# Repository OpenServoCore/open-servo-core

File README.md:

<p align="center">
  <picture>
    <source media="(prefers-color-scheme: dark)" srcset="docs/logo-dark.svg">
    
  </picture>
</p>

# OpenServoCore

> An open platform for turning cheap servos into smart actuators.

OpenServoCore (OSC) is open hardware and firmware that drops a CH32V006 control board into a $2-3 cloned hobby servo (SG90 and friends) and turns it into a Dynamixel-class smart actuator with position feedback, current sensing, bus addressing, and programmability. The bus speaks the **osc-native protocol**, a break-framed wire protocol designed to run whole on sub-$0.20 MCUs ([design writeup](https://aaronqian.com/log/2026-08-08-servo-protocol-stream-processing/)).

The thesis is the price point. At mass-production volume, an OSC swap board should add **no more than ~$1 to the BOM** of a cloned servo. That is cheap enough that upgrading every servo in a robot to smart becomes the default instead of a premium decision.

If you are here for a board, jump to [Boards](#boards). The firmware and its progress are in [Firmware](#firmware), and the design writeups are in [Reading](#reading).

## Status

**In active development. Nothing here is shippable yet.** What exists today:

- The **OSC Dev CH32** dev board is validated (Rev B) and you can order one.
- The firmware's protocol and bus transport are implemented and bench-proven on real silicon. Control loops are next.
- **[tinyboot](https://github.com/OpenServoCore/tinyboot)**, the OSC bootloader, has shipped v0.4.0 as its own repo.

The servo swap board (the one that goes inside a servo) is designed but not spun yet.

## Boards

**OSC Dev CH32** (`hardware/boards/osc-dev-v006/`) is the firmware development platform. It accepts any gutted hobby servo, takes power from USB-C, 1S-2S LiPo, or a WCH-LinkE, and fans out every rail and signal to edge test points. Rev B is validated. The [board README](hardware/boards/osc-dev-v006/README.md) has full schematics, pinouts, jumper behaviour, and bringup notes.

Want one? The full KiCad design files live in `hardware/boards/osc-dev-v006/`, ready to send to the board house of your choice.

There is also an experimental BLDC variant (`osc-dev-m007`) in the tree. It is unvalidated, so don't fab it.

## Firmware

The firmware is written in Rust and lives in `firmware/`. It is organized as chip-agnostic library crates (protocol, drivers, control table, discrete-event integration tests), a CH32 chip crate, and board binaries. The chip-agnostic layers compile and unit-test on a desktop with no hardware attached, and a discrete-event simulation runs the production crates ([the architecture writeup](https://aaronqian.com/log/2026-08-01-chip-agnostic-architecture-bare-metal-rust/) covers how).

What works today is the osc-native protocol and the servo bus transport. On the bench that means 0.5-3 Mbaud multi-servo status chains, ~30 µs ping turnaround at 1 Mbaud, and hardware CRC in both directions. The register-table conventions (flat control table, staged writes, alert semantics) will feel familiar if you have used Dynamixel. Control loops, persistence, and safety features are in progress, and build instructions will appear as the firmware matures.

Release and bench images are built with `scripts/build-image.sh <rev>` (add `--bench` for the bench-feature app, `--window` for the bench app with the window record). It exports the commit to one fixed directory (`$OSC_BUILD_ROOT`, default `~/.cache/osc-build`), builds every board image there and prints each image's sha1. The fixed path matters: cargo hashes the absolute path of each path dependency outside the workspace being built into crate metadata, rustc orders functions by the resulting symbol names, and so one commit built from two checkout paths links two layouts. On the V006 a layout shift moves timing by tens of cycles, so every image that is flashed, priced or compared comes from the script. [V006 performance](docs/v006-performance.md) covers the fetch model, the code-shape guards and how to measure a change.

The bootloader, [tinyboot](https://github.com/OpenServoCore/tinyboot), is a separate repo. It is part of the OSC firmware stack but versioned and released independently, and it supports more chips than the OSC boards on purpose (V003 / V00x / V103).

## Reading

The deep-dive writeups live on the blog:

- **[Stream processing on the wire](https://aaronqian.com/log/2026-08-08-servo-protocol-stream-processing/)**: the osc-native protocol design, and how the servo replies in tens of microseconds on a $0.16 chip.
- **[A chip-agnostic architecture for bare-metal embedded Rust](https://aaronqian.com/log/2026-08-01-chip-agnostic-architecture-bare-metal-rust/)**: the full firmware architecture, layer by layer, with code.
- **[Using the SPI peripheral as a DMA-fed CRC engine](https://aaronqian.com/log/2026-07-25-spi-as-dma-crc-engine/)**: hardware CRC on a chip with no CRC peripheral.
- **[HSI trim: calibrating a crystalless MCU over the bus](https://aaronqian.com/log/2026-07-18-hsi-trim-crystalless-mcu/)**: fleet clock calibration with nothing but the bus wire.
- **[Dynamixel 2.0 servo side: RX timing](https://aaronqian.com/log/2026-07-04-dynamixel-servo-side-rx-timing/)** and **[Fast Sync/Bulk Read](https://aaronqian.com/log/2026-07-11-dynamixel-servo-side-fast-sync-bulk-read/)**: the reference pair if you are building a Dynamixel-compatible device.

There is also one design doc in the repo worth reading. [Control theory](docs/control-theory.md) lays out the control design for the servo, with the cascaded loops, the estimators, and the sensing tiers. It is the plan, written ahead of the implementation, and it is not implemented yet.

## AI Use

I use AI heavily in this project. Claude (Fable 5, Opus 5, and earlier models) does a lot of the code generation and most of the document drafting, including parts of this README.

That does not make this vibe-coded. I review every line before it lands, and the result has to survive checks that don't care how the code was written. CI builds and tests every crate and cross-builds every board image. A discrete-event simulation runs the production crates and caught over a dozen real bugs before they reached silicon. The transport numbers above were measured on the bench. And this project was not built in one prompt. The history spans multiple years and many revisions of both the hardware and the firmware.

The documentation is more uneven than the code, and even this README could be easier to consume. That will improve, but working firmware comes first.

## Contributing

This is early. The most useful thing right now is **following along and asking questions** rather than opening PRs.

- **Discussions:** [github.com/OpenServoCore/open-servo-core/discussions](https://github.com/OpenServoCore/open-servo-core/discussions) is where design questions, ideas, and "is this on the roadmap?" go.
- **Build journey:** posts at [aaronqian.com](https://aaronqian.com) document the design decisions, dead ends, and what shipped each week.
- **Issues:** open ones are scoped to specific work. For now, contributor scope is small.

## License

OSC is fully open source.

- **Firmware**: [MIT](LICENSE-MIT) **OR** [Apache-2.0](LICENSE-APACHE), at your option (Rust ecosystem convention).
- **Hardware** (schematics, layouts, board files): [CERN-OHL-P v2.0](LICENSE-HARDWARE).

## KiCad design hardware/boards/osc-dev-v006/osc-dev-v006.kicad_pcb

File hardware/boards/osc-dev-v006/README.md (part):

# OSC Dev V006 - Rev. 2A

> **Built and brought up.**
> Rev. 2A board #1 runs an MG90 on 2S. Position calibration, the position table, motor identification and closed-loop verify all pass on it, and the sense chain is graded in [Measured on board #1](#measured-on-board-1).
> Not exercised yet: the encoder inputs (J6 / J11), Qwiic, and the second position channel. Rev. 2A also stays open for value changes that need no routing change, so the BOM can still move; see [Still open](#still-open).
> **Fabricate this at your own risk!**

See [CHANGELOG.md](CHANGELOG.md) for revision history.

This is the OpenServoCore firmware development and validation board. It is built around the CH32V006F8P6 and designed to accept any gutted hobby servo (SG90, MG90, and similar), so firmware can be brought up and characterized against real motor / pot / encoder hardware.

KiCad render of Rev. 2A.

## Overview

- **MCU** - CH32V006F8P6 (RISC-V, 48 MHz, 62 KB flash, 8 KB RAM, TSSOP20). Every pin is used, including the reset pin.
- **Motor driver** - TI DRV8212PDSGR (U3). H-bridge with IN1/IN2 PWM. 4 A peak, VM 1.65-11 V. Continuous current is thermally limited on this layout to about 1.4 A at room temperature; the exposed pad sits on the top-only `PGND` island and dumps heat through the prepreg into the ground plane, not into a copper plane of its own.
- **Current sense** - 60 mOhm kelvin-connected low-side shunt (Rs1) feeding the MCU's on-chip op-amp in bare mode. An external four-resistor difference network sets G = 14.88 against a 1.10 V bias, so both current directions are visible.
- **LDO** - HT7533-1 (U1) for the 3.3 V logic rail. No thermal shutdown, and its 500 mW budget at 2S caps the `+3V3` load at about 55 mA, board included, so keep add-ons on the 3V3 pins light and mind probe slips on the 3V3 headers. The DRV8212P VCC (`+3V3_DRV`) hangs off the same `+3V3` as the MCU through Rh2, a fitted 0R that a ferrite can replace.
- **Servo bus** - single-wire half-duplex UART on `PC0`, wired straight to the MCU through a 33 Ohm series resistor. No buffer, no TX_EN. Direction turnaround and RX timing are firmware's job.
- **Telemetry** - no dedicated pin. Telemetry rides the `DATA` wire as bounded CRC'd bursts, so there is no second UART on the board.
- **Qwiic** - SH 1.0 mm 4P I2C connector (J3) for an encoder module, either magnetic (I2C) or a quadrature encoder breakout.
- **Power input** - 1S-2S LiPo (3.0-8.4 V) via JST-PH, or the WCH-LinkE 5 V rail. Either or both, OR'd through SS54 Schottkys (about 0.25 V drop).
- **Debug** - WCH-LinkE over the CH32V006 1-wire SWDIO, on a 1x03 header (J2).
- **Position feedback** - potentiometer or analog magnetic encoder on J5, I2C encoder on J3, or an ADC-sampled IR encoder on J6 (pins) or J11 (flex landing).
- **Supply and terminal sense** - `VSYS` measured directly through its own divider, plus both motor terminals referenced to a common bias so back-EMF is readable while the bridge coasts.
- **Temperature** - onboard NTC (TH1) or external NTC (J7), selected with JP2.
- **Board** - 50 x 40 mm, 6-layer 1.6 mm (JLCPCB JLC06161H-3313 stackup), ENIG, via-in-pad.

### Changed from Rev. B

Rev. 2A is a big respin. Here is what changed:

- The 74LVC2G241 UART buffer is deleted. The bus `DATA` line connects straight to the MCU through a 33 Ohm series resistor (Rx1), and RX timing moved fully into firmware.
- Current sense is reworked around the CH32V006's on-chip op-amp: kelvin shunt, external difference network, and a VREF bias for bidirectional current.
- Motor terminal sense divider bottoms return to a bias node (`VB`) instead of GND, so both terminals stay readable during coast.
- `VSNS` is back, on its own pin, as a direct divider off `VSYS`.
- USB-C and screw-terminal power inputs are dropped. Battery and LinkE 5 V remain.
- The PWM servo header is dropped. Qwiic (I2C) is added.
- The edge test-point hook rails are replaced by nine 1.0 mm probe pads, most of them in two rows next to the sense network. See [Test points](#test-points--probing).
- 4 layers to 6 layers, and all connectors are renumbered.

## MCU pinout

CH32V006F8P6, TSSOP20. The "Function used" column is what the board wires the pin for.

|Pin|Port|Net|Function used|
|---|---|---|---|
|1|`PD4`|`OPA_OUT`|Op-amp output (`OPO0`). The same pin is ADC `A7`, which samples it.|
|2|`PD5`|`VSNA`|ADC `A5`, motor terminal A sense.|
|3|`PD6`|`VSNB`|ADC `A6`, motor terminal B sense.|
|4|`PD7`|`RST`|`nRST` from the factory. After the option byte flip it becomes the op-amp `+` input (`OPP1`) through JP1. See [First boot](#first-boot).|
|5|`PA1`|`VPOS1`|ADC `A1`, position channel 1: pot wiper or the first transducer output (RC-filtered).|
|6|`PA2`|`VPOS2_NTC`|ADC `A0`, position channel 2 for a dual-transducer sensor, or the NTC divider when JP2 is jumped.|
|7|-|`GND`|`VSS`.|
|8|`PD0`|`OPA_N`|Op-amp `-` input (`OPN1`), difference network summing node.|
|9|-|`+3V3`|`VDD`.|
|10|`PC0`|`DATA`|USART1 TX (remap 3), half-duplex (HDSEL) servo bus. Also TIM2 CH1 (remap 4) as the input of the bus break wake.|
|11|`PC1`|`SDA`|I2C1 SDA, Qwiic (J3).|
|12|`PC2`|`SCL`|I2C1 SCL, Qwiic (J3).|
|13|`PC3`|`DRV_EN`|GPIO to the DRV8212P nSLEEP. A 10K pulldown (Rh1) keeps the driver asleep at reset.|
|14|`PC4`|`VSNS`|ADC `A2`, `VSYS` supply divider.|
|15|`PC5`|`DRV_IN2`|TIM1 CH2 (remap 8), H-bridge PWM.|
|16|`PC6`|`DRV_IN1`|TIM1 CH3 (remap 8), H-bridge PWM.|
|17|`PC7`|`STAT`|STAT LED, active low, driven as a plain GPIO. The only firmware-driven lamp.|
|18|`PD1`|`SWDIO`|1-wire debug, 100 Ohm series (Ru1) to J2.|
|19|`PD2`|`ENCB`|Encoder B. ADC `A3`, analog quadrature sampling.|
|20|`PD3`|`ENCA`|Encoder A. ADC `A4`, analog quadrature sampling.|

TIM1 runs center-aligned PWM on IN1/IN2 at 20 kHz, and its update event triggers the ADC scans at the counter crest and trough (see [PWM and ADC timing](#pwm-and-adc-timing)). Remap 8 puts TIM1 CH4 on `PC7`, but CH4 is unused and STAT is a GPIO.

## Connectors

All 2.54 mm pin headers are vertical through-hole.

### Battery - J1

JST-PH 2P horizontal. **1S-2S LiPo only (3.0-8.4 V).** The DRV8212P caps the safe motor rail at 11 V, so 3S is not supported. This input is OR'd into `VSYS` through an SS54 (Dp1), so it coexists with LinkE power.

### WCH-LinkE - J2

1x03 pin header (2.54 mm) for the WCH-LinkE programmer / debugger.

|Pin|Net|Notes|
|---|---|---|
|1|`VPROG`|LinkE 5 V rail, OR'd into `VSYS` through an SS54 (Dp2).|
|2|`GND`||
|3|`SWDIO`|1-wire debug, through a 100 Ohm series resistor (Ru1).|

Three pins is the whole header now. Telemetry rides the servo bus, so the LinkE's TX / RX are not connected to anything.

Plugging in the LinkE alone is enough to power the board. Very handy for firmware-only sessions.

### Qwiic - J3

SH 1.0 mm 4P (GND / +3V3 / SDA / SCL), standard [Qwiic](https://www.sparkfun.com/qwiic) pinout. 4K7 pull-ups (Rq1 / Rq2) sit on the MCU side, and 100 Ohm series resistors (Rq3 / Rq4) sit between the MCU and the connector.

This one is meant for an encoder module rather than generic sensors: an I2C magnetic encoder (MT6701 / AS5600 breakout) or a quadrature encoder adapter. The board has no hardware quadrature counting (see J6), so Qwiic is the flexible stand-in for it. I2C1 is polled.

### Motor - J4

1x02 pin header carrying `MOT_A` / `MOT_B` straight off the DRV8212P outputs. Through-hole, so the high-current path stays zero-via.

### Position - J5

1x04 pin header, `+3V3` / `GND` / `POS1` / `POS2`. It takes:

- The gutted servo's **potentiometer** on `POS1`. Excitation comes from `+3V3` and the wiper goes into `POS1`. Excitation and ADC reference share the same rail, so the reading is ratiometric and supply drift cancels out.
- An **analog-output magnetic encoder** (e.g. MT6701 in ratiometric analog mode) as a drop-in pot replacement on the same first three pins.
- A **dual-output transducer** (sin / cos style, the tier-2 sensor) on `POS1` and `POS2`. `POS2` shares its ADC pin with the NTC, so leave JP2 open in this mode; the on-board temperature reading is given up for the second channel. Both channels sit behind identical 4K7 / 100nF filters (Ra1 / Ca1 and Ra2 / Ca2) so the pair stays phase-matched.

With a pot or a single-output encoder, leave `POS2` unconnected and jump JP2 for the NTC. For a digital magnetic encoder use Qwiic (I2C) instead.

### Encoder - J6

2x02 pin header. `+3V3` / `GND` on one row, `ENCA` / `ENCB` on the other, going into ADC channels `A4` / `A3`. Silk reads `QA` / `QB` for the two phases.

This is a future expansion connector for an ADC-sampled custom IR quadrature encoder, in the style of [ServoProject](https://github.com/adamb314/ServoProject). The analog A/B phases get oversampled and interpolated for sub-count resolution. Hardware quadrature counting is not possible here since `PD2` / `PD3` don't carry TIM2 CH1/CH2, so I never considered it. A digital encoder belongs on Qwiic instead.

### Motor encoder flex - J11

Six bare pads at 1.0 mm pitch for the motor-shaft encoder flex, attached tin-and-iron: the flex fingers are pre-tinned, laid on the pads and pressed with an iron, then hot glue over the pad row takes the strain. The footprint pair (`Flex_Landing_1x06_P1.0mm` on the board, `Flex_Fingers_1x06_P1.0mm` on the flex) lives in the shared library, and the same landing goes on the swap board, so the dev board rehearses the real attach. Pin 1 is at the bracket mark.

|Pin|Net|Notes|
|---|---|---|
|1|`GND`|Outer ground, guards the pair.|
|2|`+3V3`|Emitter and phototransistor supply.|
|3|`ENCA`|IR sensor A, ADC `A4`. Same net as J6. Silk `QA`.|
|4|`ENCB`|IR sensor B, ADC `A3`. Same net as J6. Silk `QB`.|
|5|`VNTC_EXT`|Thermistor on the motor can, into the external leg of JP2. The divider resistor sits on the flex. Silk `NTC`.|
|6|`GND`|Outer ground.|

J6 and J11 are the same encoder input in two shapes: pins for a wired breakout or the bench coupon, the landing for the flex. Populate one.

### External NTC - J7

1x03 pin header, `VNTC_EXT` / `+3V3` / `GND`, for an external NTC thermistor or temperature sensor. Select it with JP2. The `+3V3` pin is there so the external part can bring its own pull-up or supply: a bare thermistor divides against a resistor on the connector, a sensor with a driven output just takes the rail. Rn1 10K serves the internal TH1 leg only, so nothing on the board loads the external node. The firmware's NTC constants (10K pull-up, 10K / 3950 part) describe the onboard divider, so a bare 10K / 3950 thermistor on J7 takes the same conversion when a 10K from the J7 `+3V3` pin to `VNTC_EXT` divides against it.

### Servo TTL bus - J8 / J9 / J10

OpenServoCore talks over a single-wire half-duplex UART, the same electrical layer as a TTL servo bus. Three wires only (`GND` / `V+` / `DATA`), the same pin count as a hobby servo cable. The wire protocol on top is **osc-native**, OSC's own break-framed protocol built for sub-$0.20 MCUs ([spec](../../../docs/osc-native-protocol.md)).

Three connectors share the same nets. Pick whichever fits your wiring:

- **J8** - 1x03 pin header for breadboard / daisy-chain wiring.
- **J9, J10** - JST-PH 3P vertical for cables.

Pin order is `G` / `V` / `D` with `V` in the center, so a reversed bench header only swaps `DATA` and `GND`, never power.

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
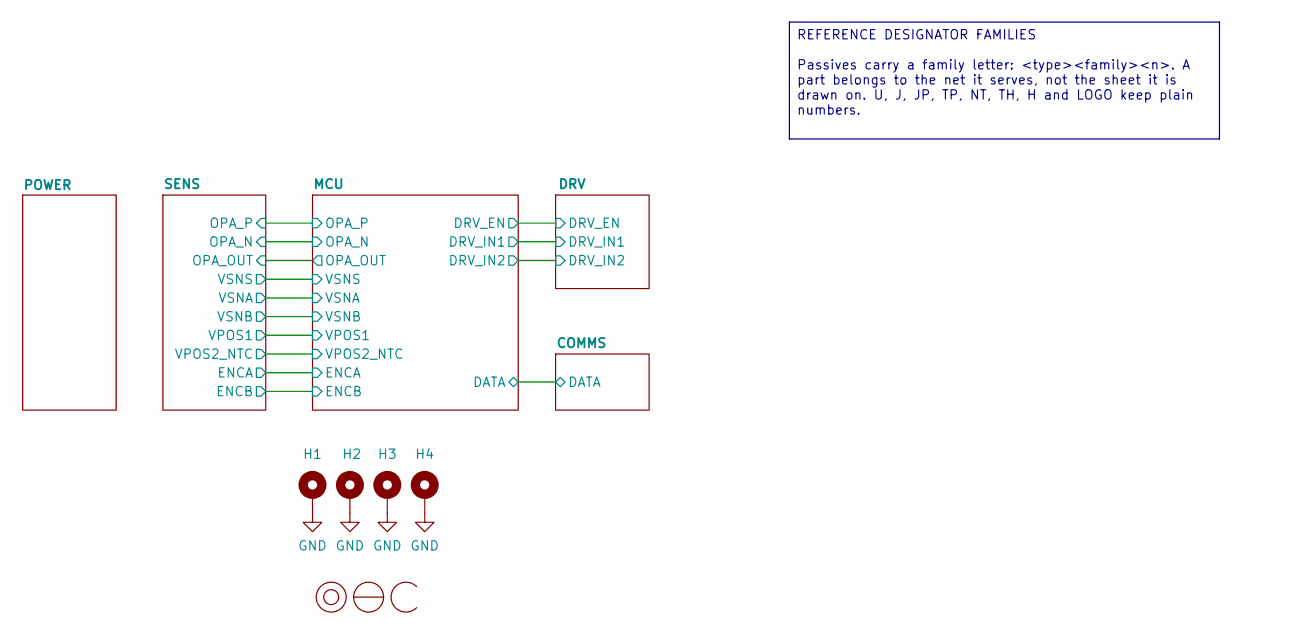
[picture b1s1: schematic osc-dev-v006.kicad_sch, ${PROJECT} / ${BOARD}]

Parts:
H1, H2, H3, H4: MountingHole_Pad_MP; MountingHole_2.2mm_M2_ISO7380_Pad
LOGO1: osc-logo; osc

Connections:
GND: H1.1 (1_1), H2.1 (1_1), H3.1 (1_1), H4.1 (1_1); also elsewhere on the board

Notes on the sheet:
REFERENCE DESIGNATOR FAMILIES Passives carry a family letter: <type><family><n>. A part belongs to the net it serves, not the sheet it is drawn on. U, J, JP, TP, NT, TH, H and LOGO keep plain numbers.

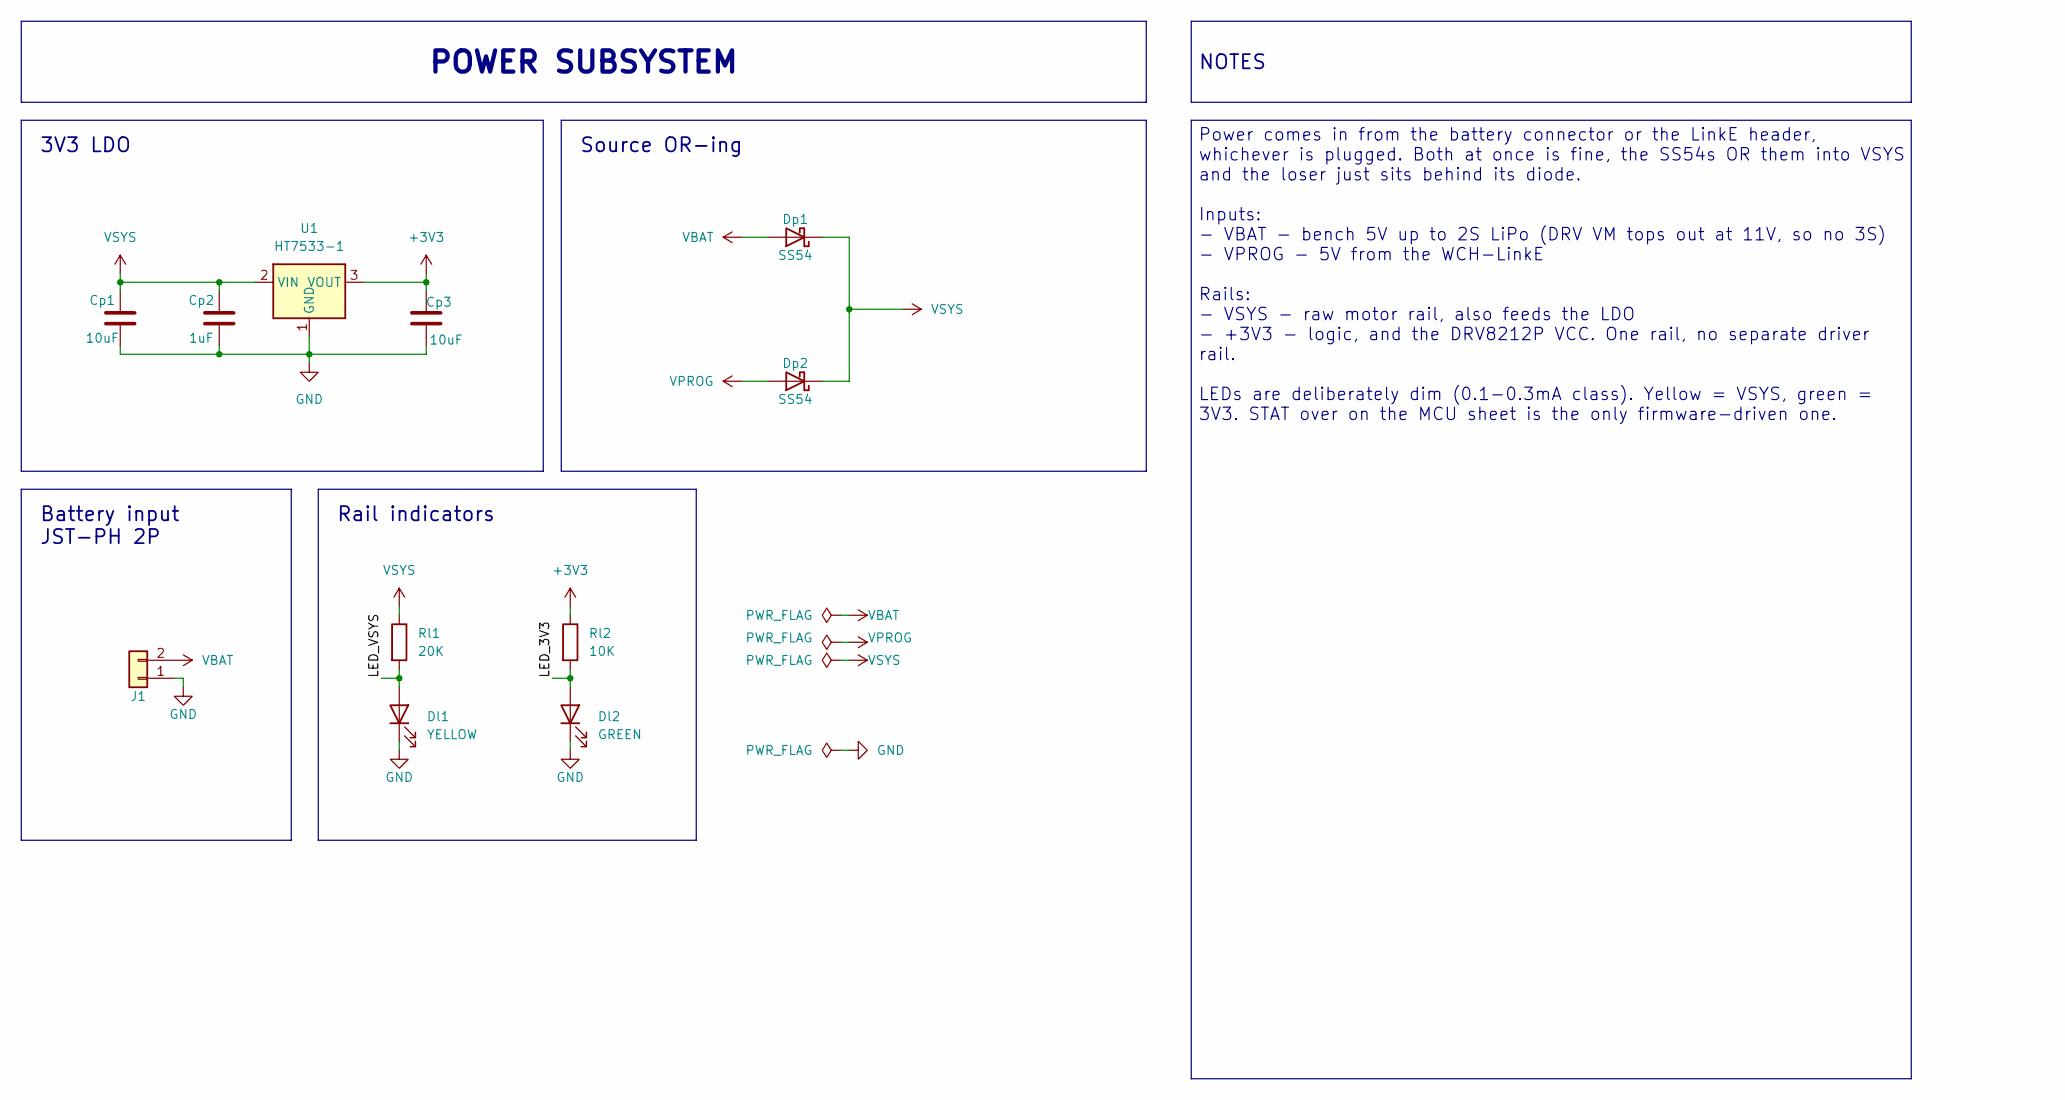
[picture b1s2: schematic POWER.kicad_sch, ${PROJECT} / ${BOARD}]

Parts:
Cp1, Cp3: 10uF; C_0805_2012Metric_Pad1.18x1.45mm_HandSolder; LCSC C15850
Cp2: 1uF; C_0603_1608Metric_Pad1.08x0.95mm_HandSolder; LCSC C559769
Dl1: YELLOW; LED_0603_1608Metric_Pad1.05x0.95mm_HandSolder; LCSC C497929
Dl2: GREEN; LED_0603_1608Metric_Pad1.05x0.95mm_HandSolder; LCSC C497927
Dp1, Dp2: SS54; D_SMA_Handsoldering; LCSC C22452
J1: JST-PH-H; CONN-TH_S2B-PH-K-S-LF-SN; LCSC C173752
Rl1: 20K; R_0603_1608Metric_Pad0.98x0.95mm_HandSolder; LCSC C2907011
Rl2: 10K; R_0603_1608Metric_Pad0.98x0.95mm_HandSolder; LCSC C2906982
U1: HT7533-1; SOT-89-3_Handsoldering; LCSC C14289

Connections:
+3V3: Cp3.1, Rl2.1, U1.3 (VOUT); also elsewhere on the board
/POWER/LED_3V3: Dl2.2 (A), Rl2.2
/POWER/LED_VSYS: Dl1.2 (A), Rl1.2
GND: Cp1.2, Cp2.2, Cp3.2, Dl1.1 (K), Dl2.1 (K), J1.1, U1.1 (GND); also elsewhere on the board
VBAT: Dp1.2 (A), J1.2
VPROG: Dp2.2 (A); also elsewhere on the board
VSYS: Cp1.1, Cp2.1, Dp1.1 (K), Dp2.1 (K), Rl1.1, U1.2 (VIN); also elsewhere on the board

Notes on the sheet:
Battery input JST-PH 2P
3V3 LDO
Rail indicators
Source OR-ing
NOTES
Power comes in from the battery connector or the LinkE header, whichever is plugged. Both at once is fine, the SS54s OR them into VSYS and the loser just sits behind its diode. Inputs: - VBAT - bench 5V up to 2S LiPo (DRV VM tops out at 11V, so no 3S) - VPROG - 5V from the WCH-LinkE Rails: - VSYS -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
POWER SUBSYSTEM

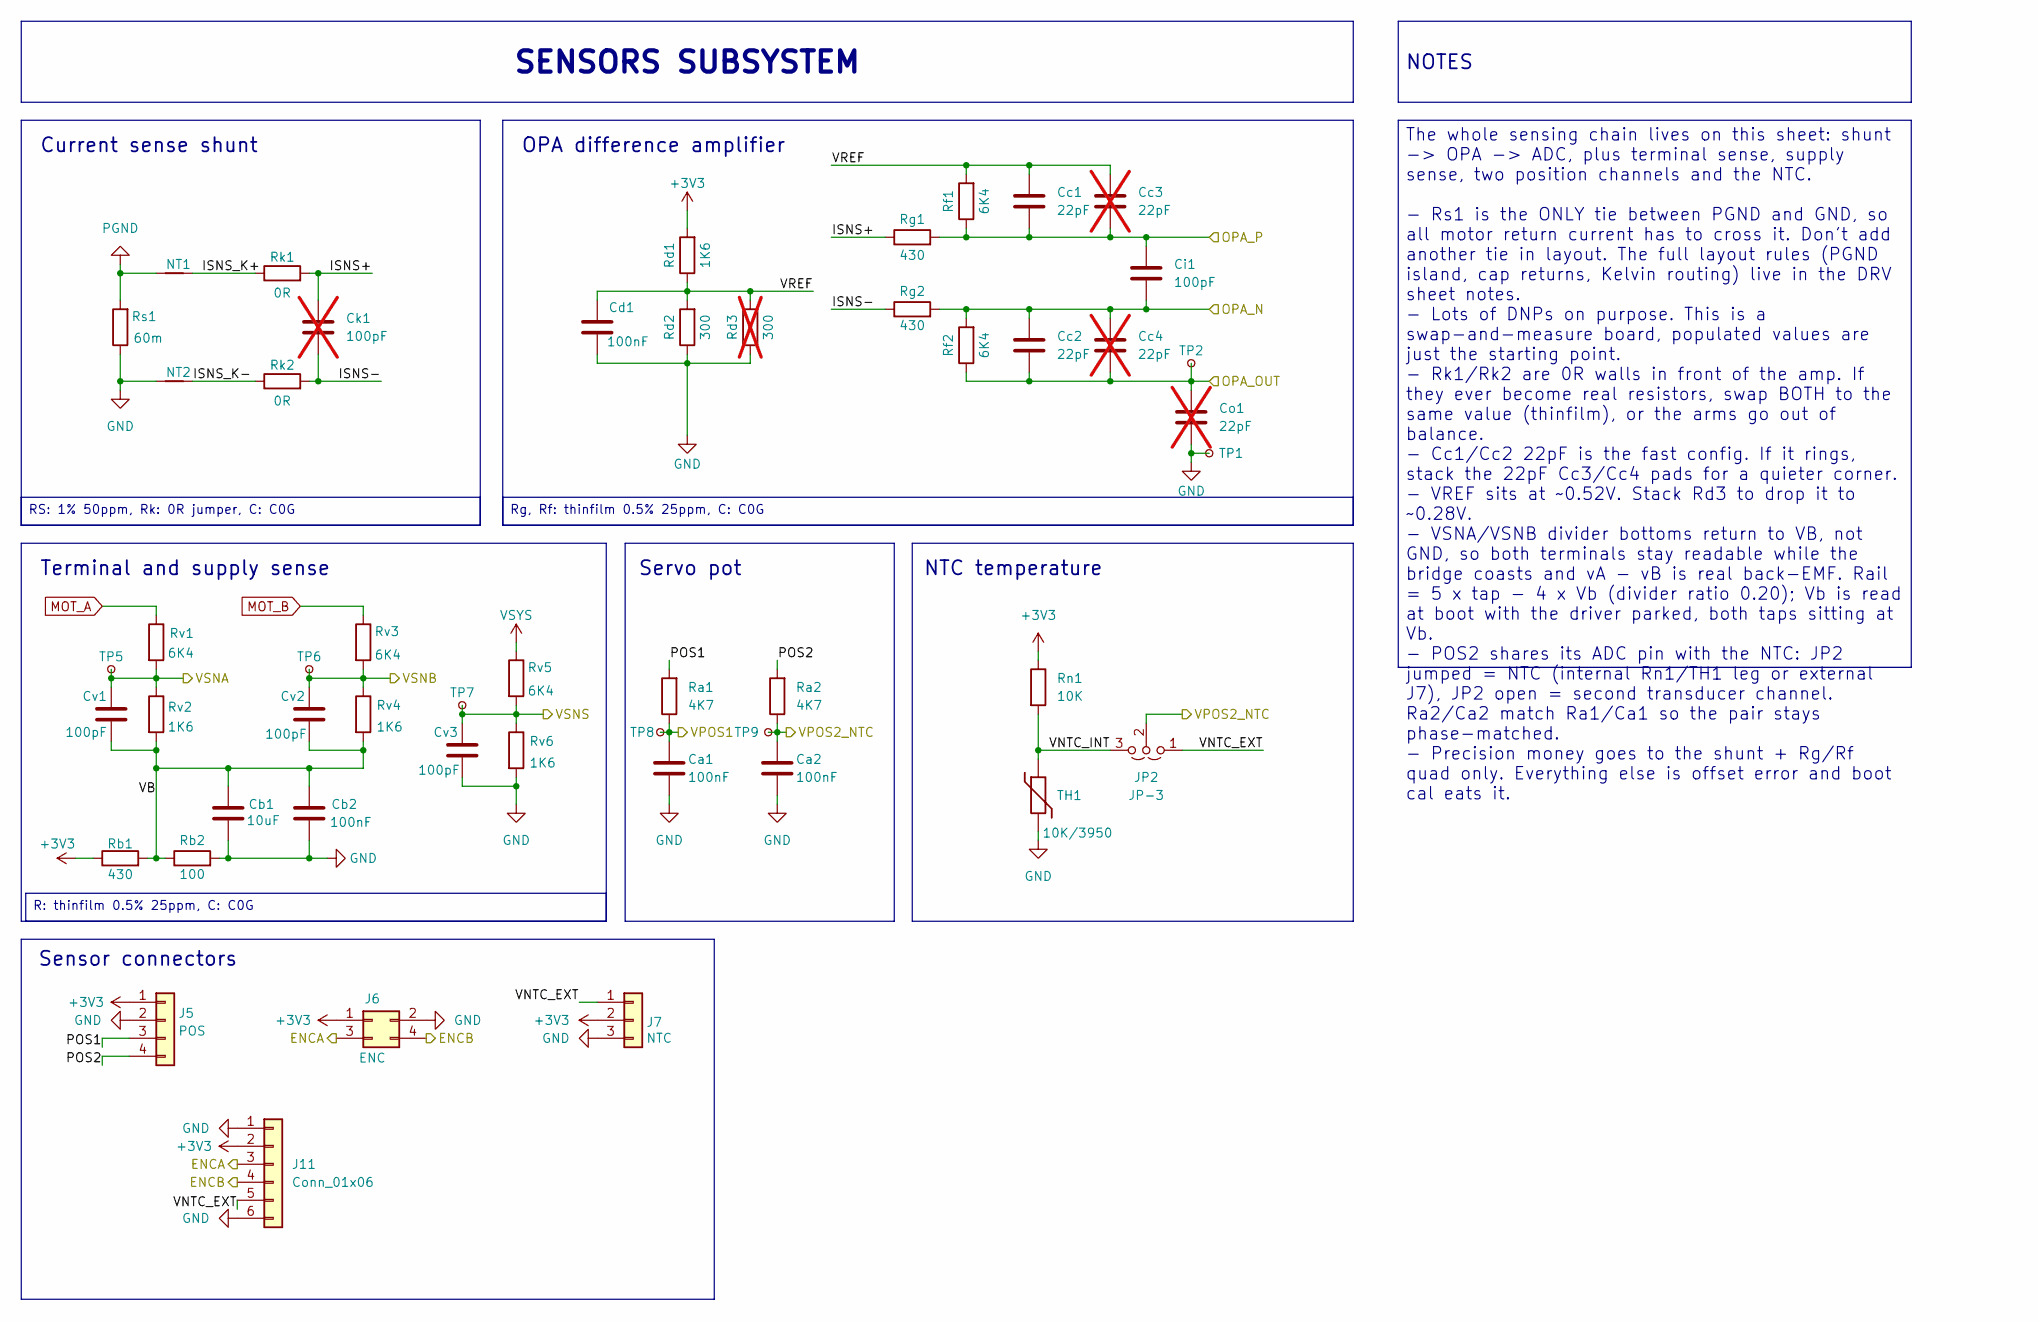
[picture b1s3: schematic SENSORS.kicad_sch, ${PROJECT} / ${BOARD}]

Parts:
Ca1, Ca2: 100nF; C_0603_1608Metric_Pad1.08x0.95mm_HandSolder; LCSC C14663
Cb1: 10uF; C_0805_2012Metric_Pad1.18x1.45mm_HandSolder; LCSC C15850
Cb2: 100nF; C_0603_1608Metric_Pad1.08x0.95mm_HandSolder; LCSC C14663
Cc1, Cc2: 22pF; C_0603_1608Metric_Pad1.08x0.95mm_HandSolder; LCSC C105620
Cc3, Cc4: 22pF; C_0603_1608Metric_Pad1.08x0.95mm_HandSolder; LCSC C105620; not fitted
Cd1: 100nF; C_0603_1608Metric_Pad1.08x0.95mm_HandSolder; LCSC C14663
Ci1: 100pF; C_0603_1608Metric_Pad1.08x0.95mm_HandSolder; LCSC C14665
Ck1: 100pF; C_0603_1608Metric_Pad1.08x0.95mm_HandSolder; LCSC C14665; not fitted
Co1: 22pF; C_0603_1608Metric_Pad1.08x0.95mm_HandSolder; LCSC C14665; not fitted
Cv1, Cv2, Cv3: 100pF; C_0603_1608Metric_Pad1.08x0.95mm_HandSolder; LCSC C14665
J5: POS; PinHeader_1x04_P2.54mm_Vertical
J6: ENC; PinHeader_2x02_P2.54mm_Vertical; LCSC C66690
J7: NTC; PinHeader_1x03_P2.54mm_Vertical; LCSC C49257
J11: Conn_01x06; Flex_Landing_1x06_P1.0mm
JP2: JP-3; PinHeader_1x03_P2.54mm_Vertical; LCSC C41425293
NT1, NT2: NetTie_2; NetTie-2_SMD_0.2mm
Ra1, Ra2: 4K7; R_0603_1608Metric_Pad0.98x0.95mm_HandSolder; LCSC C2907034
Rb1: 430; R_0603_1608Metric_Pad0.98x0.95mm_HandSolder; LCSC C374586
Rb2: 100; R_0603_1608Metric_Pad0.98x0.95mm_HandSolder; LCSC C125923
Rd1: 1K6; R_0603_1608Metric_Pad0.98x0.95mm_HandSolder; LCSC C374557
Rd2: 300; R_0603_1608Metric_Pad0.98x0.95mm_HandSolder; LCSC C374566
Rd3: 300; R_0603_1608Metric_Pad0.98x0.95mm_HandSolder; LCSC C374566; not fitted
Rf1, Rf2: 6K4; R_0603_1608Metric_Pad0.98x0.95mm_HandSolder; LCSC C374580
Rg1, Rg2: 430; R_0603_1608Metric_Pad0.98x0.95mm_HandSolder; LCSC C374586
Rk1, Rk2: 0R; R_0603_1608Metric_Pad0.98x0.95mm_HandSolder; LCSC C95177
Rn1: 10K; R_0603_1608Metric_Pad0.98x0.95mm_HandSolder; LCSC C2906982
Rs1: 60m; R_1206_3216Metric_Pad1.30x1.75mm_HandSolder; LCSC C49164944
Rv1, Rv3, Rv5: 6K4; R_0603_1608Metric_Pad0.98x0.95mm_HandSolder; LCSC C374580
Rv2, Rv4, Rv6: 1K6; R_0603_1608Metric_Pad0.98x0.95mm_HandSolder; LCSC C374557
TH1: 10K/3950; R_0603_1608Metric_Pad0.98x0.95mm_HandSolder; LCSC C2889049
TP1: GND; TestPoint_Pad_D1.0mm
TP2: OPA; TestPoint_Pad_D1.0mm
TP5: VA; TestPoint_Pad_D1.0mm
TP6: VB; TestPoint_Pad_D1.0mm
TP7: VS; TestPoint_Pad_D1.0mm
TP8: VP1; TestPoint_Pad_D1.0mm
TP9: VP2; TestPoint_Pad_D1.0mm

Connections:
+3V3: J5.1, J6.1, J7.2, J11.2, Rb1.1, Rd1.2, Rn1.1; also elsewhere on the board
/MCU/ENCA: J6.3, J11.3; also elsewhere on the board
/MCU/ENCB: J6.4, J11.4; also elsewhere on the board
/MCU/OPA_N: Cc2.1, Cc4.1, Ci1.2, Rf2.2, Rg2.2; also elsewhere on the board
/MCU/OPA_OUT: Cc2.2, Cc4.2, Co1.1, Rf2.1, TP2.1 (1_1); also elsewhere on the board
/MCU/OPA_P: Cc1.2, Cc3.2, Ci1.1, Rf1.1, Rg1.2; also elsewhere on the board
/MCU/VPOS1: Ca1.1, Ra1.1, TP8.1 (1_1); also elsewhere on the board
/MCU/VPOS2_NTC: Ca2.1, JP2.2 (C), Ra2.1, TP9.1 (1_1); also elsewhere on the board
/MCU/VSNA: Cv1.1, Rv1.2, Rv2.1, TP5.1 (1_1); also elsewhere on the board
/MCU/VSNB: Cv2.1, Rv3.2, Rv4.1, TP6.1 (1_1); also elsewhere on the board
/MCU/VSNS: Cv3.1, Rv5.2, Rv6.1, TP7.1 (1_1); also elsewhere on the board
/SENS/ISNS+: Ck1.1, Rg1.1, Rk1.2
/SENS/ISNS-: Ck1.2, Rg2.1, Rk2.2
/SENS/ISNS_K+: NT1.1, Rk1.1
/SENS/ISNS_K-: NT2.1, Rk2.1
/SENS/POS1: J5.3, Ra1.2
/SENS/POS2: J5.4, Ra2.2
/SENS/VB: Cb1.1, Cb2.1, Cv1.2, Cv2.2, Rb1.2, Rb2.1, Rv2.2, Rv4.2
/SENS/VNTC_EXT: J7.1, J11.5, JP2.1 (A)
/SENS/VNTC_INT: JP2.3 (B), Rn1.2, TH1.1
/SENS/VREF: Cc1.1, Cc3.1, Cd1.1, Rd1.1, Rd2.2, Rd3.2, Rf1.2
GND: Ca1.2, Ca2.2, Cb1.2, Cb2.2, Cd1.2, Co1.2, Cv3.2, J5.2, J6.2, J7.3, J11.1, J11.6, NT2.2, Rb2.2, Rd2.1, Rd3.1, Rs1.1, Rv6.2, TH1.2, TP1.1 (1_1); also elsewhere on the board
MOT_A: Rv1.1; also elsewhere on the board
MOT_B: Rv3.1; also elsewhere on the board
PGND: NT1.2, Rs1.2; also elsewhere on the board
VSYS: Rv5.1; also elsewhere on the board

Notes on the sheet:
Terminal and supply sense
Current sense shunt
OPA difference amplifier
NTC temperature
Sensor connectors
Servo pot
Rg, Rf: thinfilm 0.5% 25ppm, C: C0G
SENSORS SUBSYSTEM
NOTES
R: thinfilm 0.5% 25ppm, C: C0G
The whole sensing chain lives on this sheet: shunt -> OPA -> ADC, plus terminal sense, supply sense, two position channels and the NTC. - Rs1 is the ONLY tie between PGND and GND, so all motor return current has to cross it. Don't add another tie in layout. The full layout rules (PGND island, cap r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
RS: 1% 50ppm, Rk: 0R jumper, C: C0G

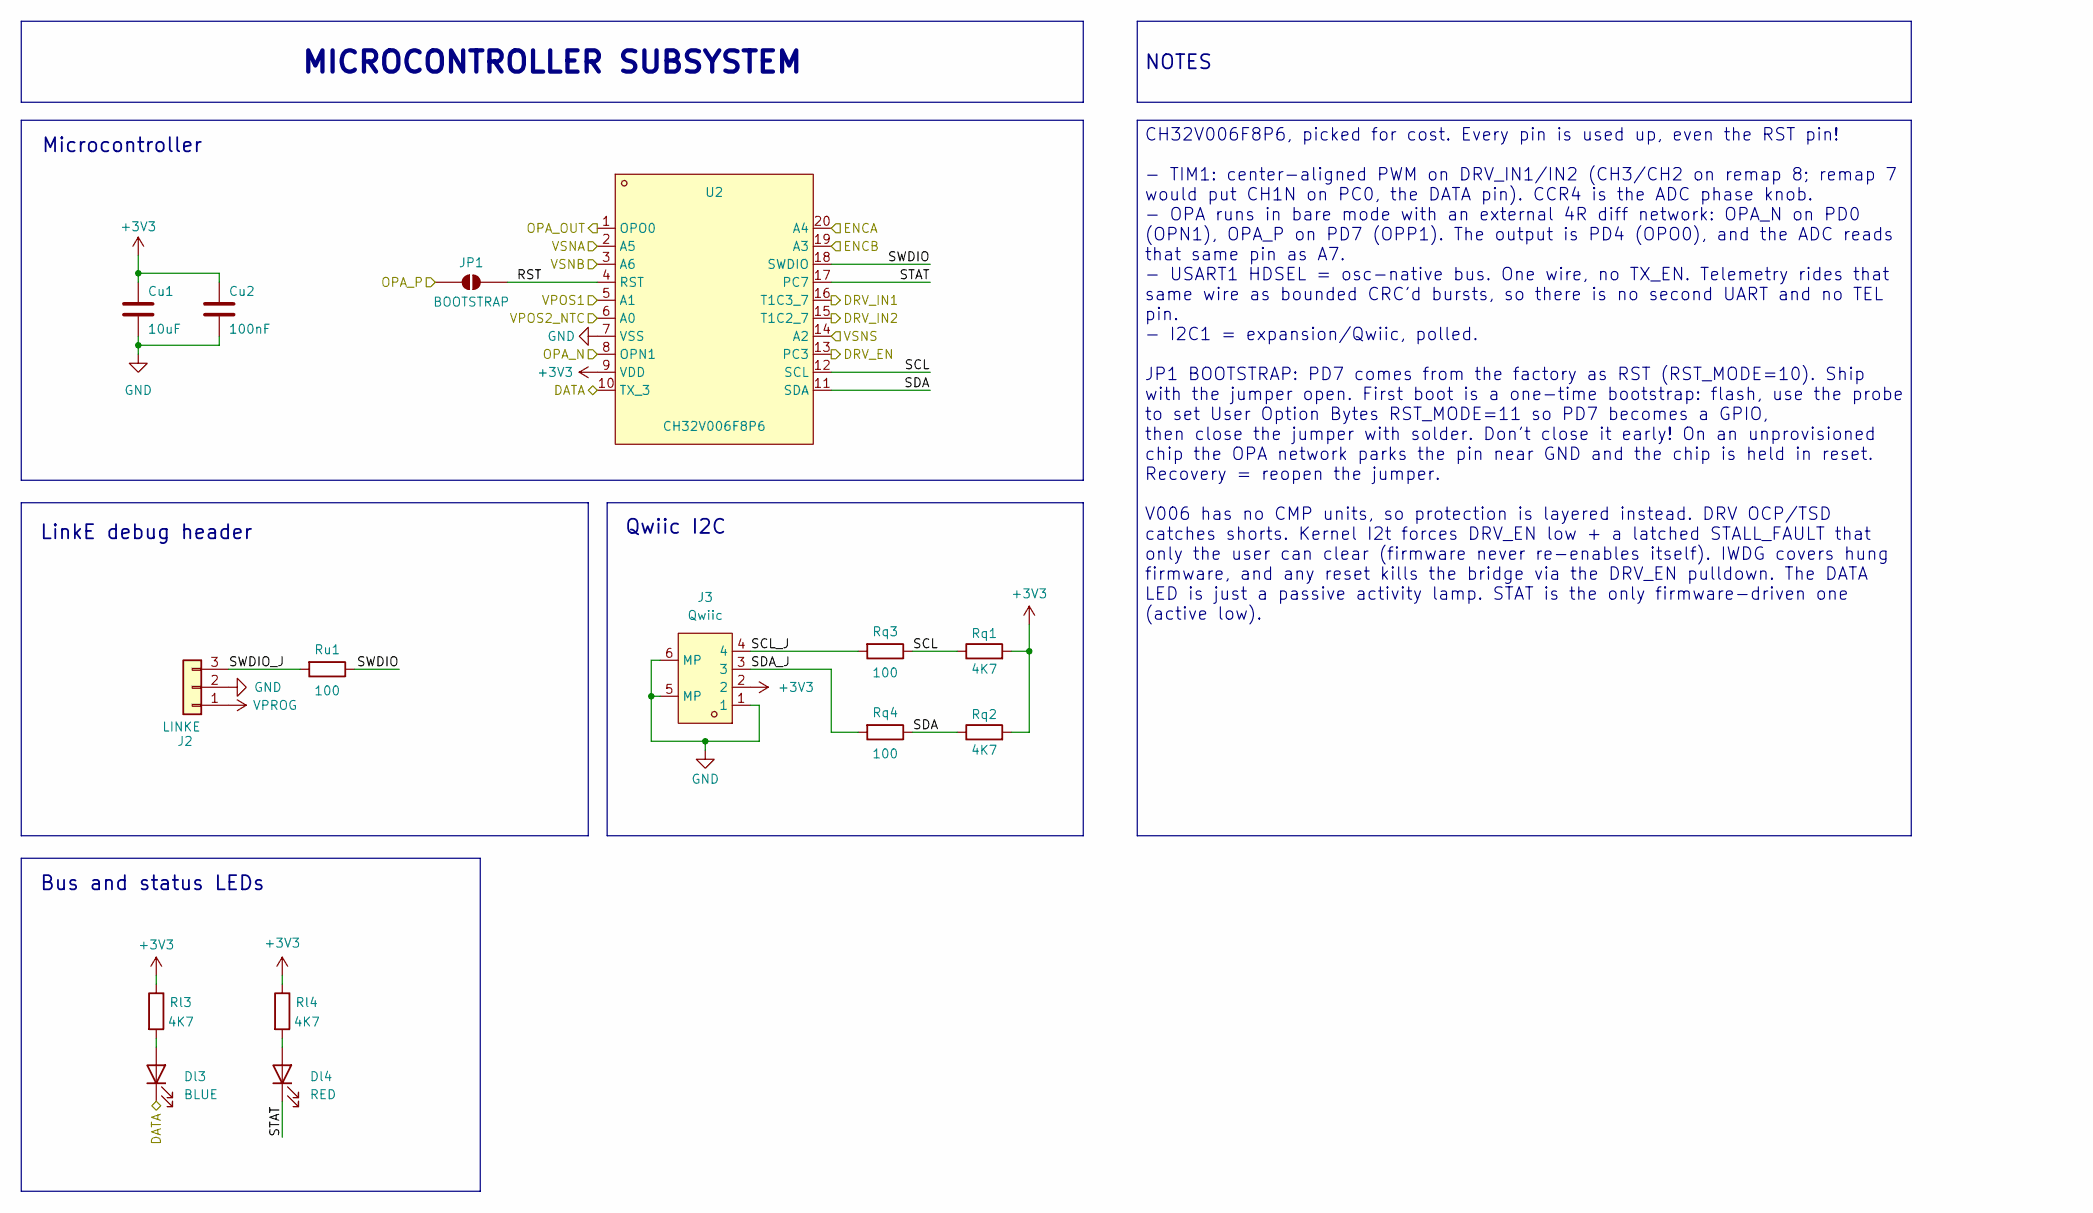
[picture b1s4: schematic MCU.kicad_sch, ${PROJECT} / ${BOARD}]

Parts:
Cu1: 10uF; C_0805_2012Metric_Pad1.18x1.45mm_HandSolder; LCSC C15850
Cu2: 100nF; C_0603_1608Metric_Pad1.08x0.95mm_HandSolder; LCSC C14663
Dl3: BLUE; LED_0603_1608Metric_Pad1.05x0.95mm_HandSolder; LCSC C51933294
Dl4: RED; LED_0603_1608Metric_Pad1.05x0.95mm_HandSolder; LCSC C497918
J2: LINKE; PinHeader_1x03_P2.54mm_Vertical; LCSC C49257
J3: Qwiic; CONN-SMD_SH1.0MM-4P-WT; LCSC C53055320
JP1: BOOTSTRAP; SolderJumper-2_P1.3mm_Open_TrianglePad1.0x1.5mm
Rl3, Rl4: 4K7; R_0603_1608Metric_Pad0.98x0.95mm_HandSolder; LCSC C2907034
Rq1, Rq2: 4K7; R_0603_1608Metric_Pad0.98x0.95mm_HandSolder; LCSC C2907034
Rq3, Rq4: 100; R_0603_1608Metric_Pad0.98x0.95mm_HandSolder; LCSC C125923
Ru1: 100; R_0603_1608Metric_Pad0.98x0.95mm_HandSolder; LCSC C125923
U2: CH32V006F8P6; TSSOP-20_4.4x6.5mm_P0.65mm; LCSC C52753342

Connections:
+3V3: Cu1.1, Cu2.1, J3.2, Rl3.1, Rl4.1, Rq1.2, Rq2.2, U2.9 (VDD); also elsewhere on the board
/COMMS/DATA: Dl3.1 (K), U2.10 (TX_3); also elsewhere on the board
/DRV/DRV_EN: U2.13 (PC3); also elsewhere on the board
/DRV/DRV_IN1: U2.16 (T1C3_7); also elsewhere on the board
/DRV/DRV_IN2: U2.15 (T1C2_7); also elsewhere on the board
/MCU/ENCA: U2.20 (A4); also elsewhere on the board
/MCU/ENCB: U2.19 (A3); also elsewhere on the board
/MCU/OPA_N: U2.8 (OPN1); also elsewhere on the board
/MCU/OPA_OUT: U2.1 (OPO0); also elsewhere on the board
/MCU/OPA_P: JP1.1 (A); also elsewhere on the board
/MCU/RST: JP1.2 (B), U2.4 (RST)
/MCU/SCL: Rq1.1, Rq3.1, U2.12 (SCL)
/MCU/SCL_J: J3.4, Rq3.2
/MCU/SDA: Rq2.1, Rq4.1, U2.11 (SDA)
/MCU/SDA_J: J3.3, Rq4.2
/MCU/STAT: Dl4.1 (K), U2.17 (PC7)
/MCU/SWDIO: Ru1.1, U2.18 (SWDIO)
/MCU/SWDIO_J: J2.3, Ru1.2
/MCU/VPOS1: U2.5 (A1); also elsewhere on the board
/MCU/VPOS2_NTC: U2.6 (A0); also elsewhere on the board
/MCU/VSNA: U2.2 (A5); also elsewhere on the board
/MCU/VSNB: U2.3 (A6); also elsewhere on the board
/MCU/VSNS: U2.14 (A2); also elsewhere on the board
GND: Cu1.2, Cu2.2, J2.2, J3.1, J3.5 (MP), J3.6 (MP), U2.7 (VSS); also elsewhere on the board
unnamed: Dl3.2 (A), Rl3.2
unnamed: Dl4.2 (A), Rl4.2
VPROG: J2.1; also elsewhere on the board

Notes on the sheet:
Microcontroller
Qwiic I2C
LinkE debug header
Bus and status LEDs
NOTES
CH32V006F8P6, picked for cost. Every pin is used up, even the RST pin! - TIM1: center-aligned PWM on DRV_IN1/IN2 (CH3/CH2 on remap 8; remap 7 would put CH1N on PC0, the DATA pin). CCR4 is the ADC phase knob. - OPA runs in bare mode with an external 4R diff network: OPA_N on PD0 (OPN1), OPA_P on PD7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
MICROCONTROLLER SUBSYSTEM

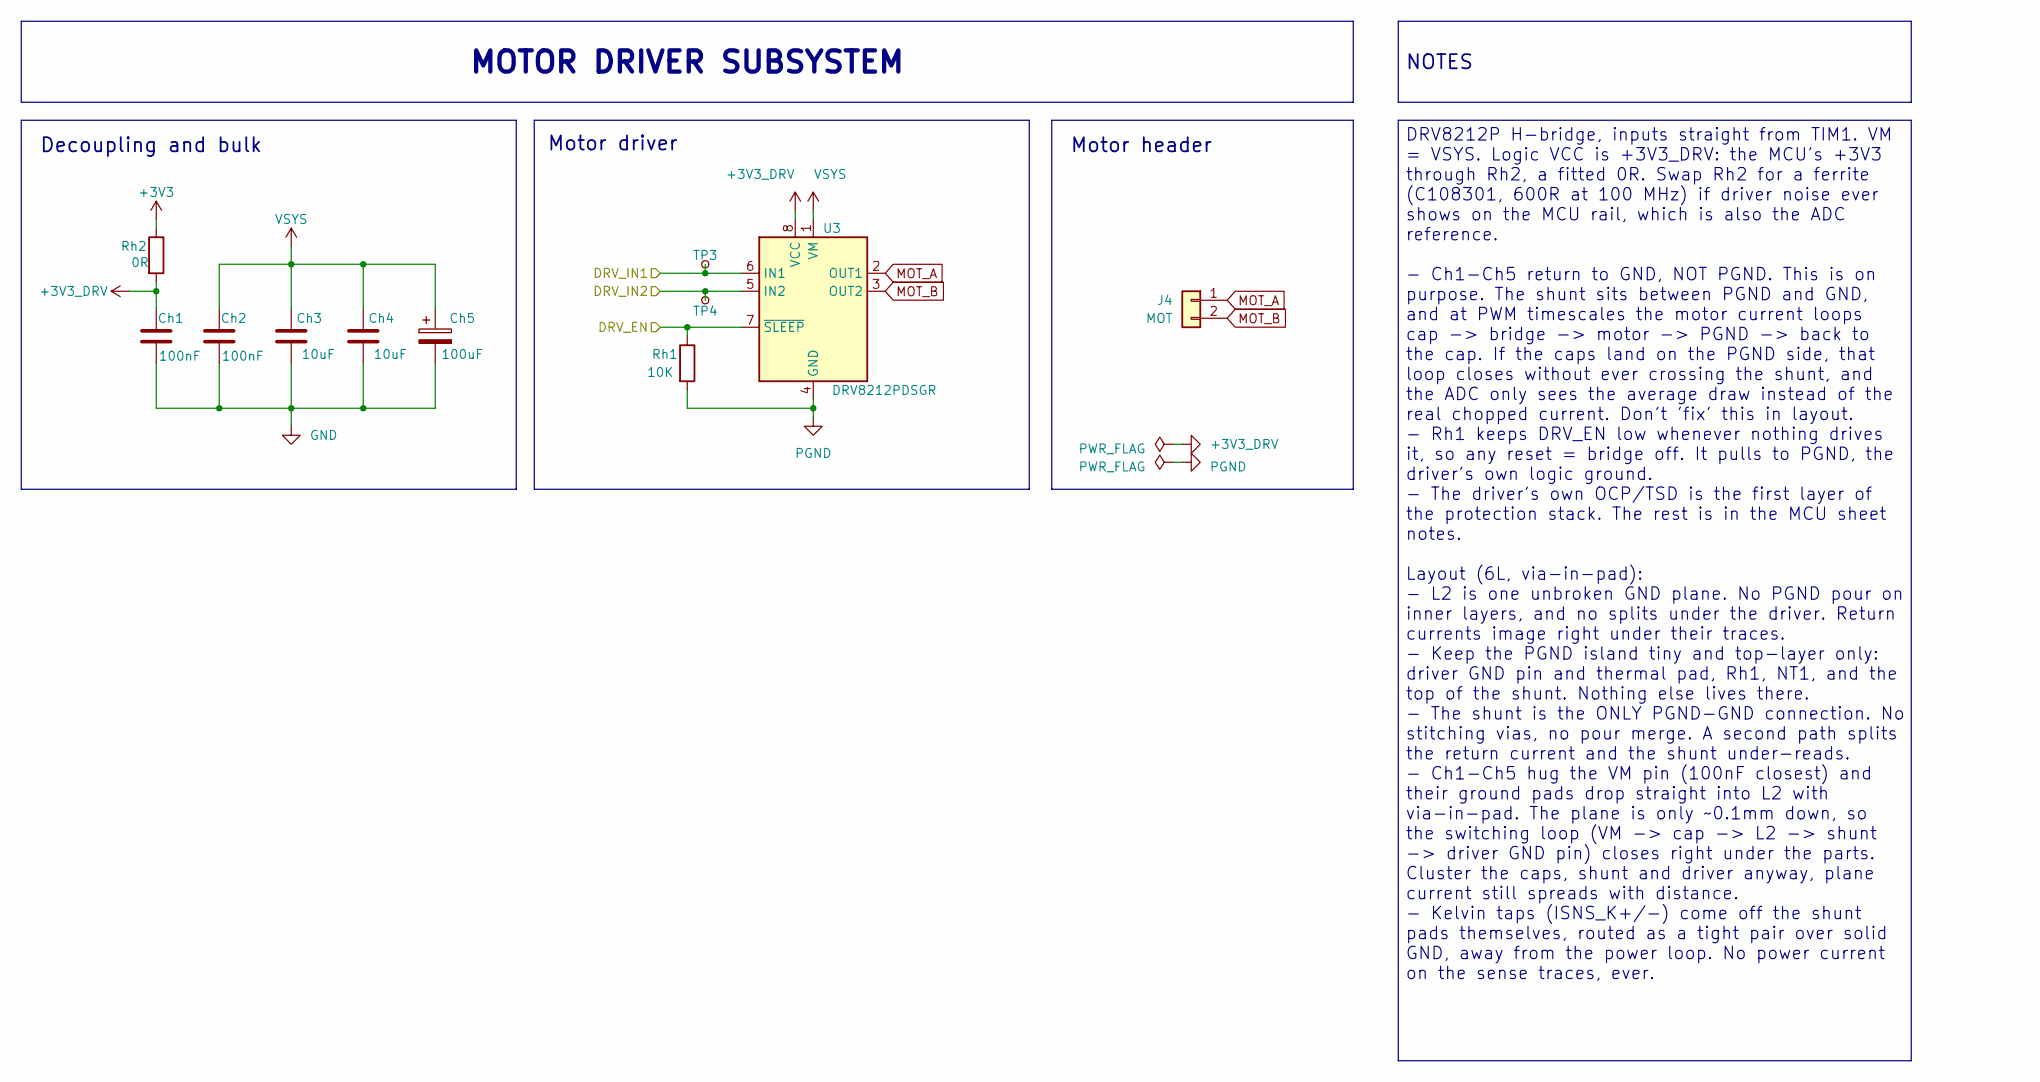
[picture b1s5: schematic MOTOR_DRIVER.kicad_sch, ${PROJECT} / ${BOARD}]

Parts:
Ch1, Ch2: 100nF; C_0603_1608Metric_Pad1.08x0.95mm_HandSolder; LCSC C14663
Ch3, Ch4: 10uF; C_0805_2012Metric_Pad1.18x1.45mm_HandSolder; LCSC C15850
Ch5: 100uF; CP_Elec_6.3x5.4; LCSC C22383777
J4: MOT; PinHeader_1x02_P2.54mm_Vertical; LCSC C492401
Rh1: 10K; R_0603_1608Metric_Pad0.98x0.95mm_HandSolder; LCSC C2906982
Rh2: 0R; R_0603_1608Metric_Pad0.98x0.95mm_HandSolder; LCSC C95177
TP3: IN1; TestPoint_Pad_D1.0mm
TP4: IN2; TestPoint_Pad_D1.0mm
U3: DRV8212PDSGR; Texas_DSG0008A_WSON-8-1EP_2x2mm_P0.5mm_EP0.9x1.6mm; LCSC C5208051

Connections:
+3V3: Rh2.1; also elsewhere on the board
+3V3_DRV: Ch1.1, Rh2.2, U3.8 (VCC)
/DRV/DRV_EN: Rh1.1, U3.7 (~SLEEP); also elsewhere on the board
/DRV/DRV_IN1: TP3.1 (1_1), U3.6 (IN1); also elsewhere on the board
/DRV/DRV_IN2: TP4.1 (1_1), U3.5 (IN2); also elsewhere on the board
GND: Ch1.2, Ch2.2, Ch3.2, Ch4.2, Ch5.2; also elsewhere on the board
MOT_A: J4.1, U3.2 (OUT1); also elsewhere on the board
MOT_B: J4.2, U3.3 (OUT2); also elsewhere on the board
PGND: Rh1.2, U3.4 (GND), U3.9 (GND); also elsewhere on the board
VSYS: Ch2.1, Ch3.1, Ch4.1, Ch5.1, U3.1 (VM); also elsewhere on the board

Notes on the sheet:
Motor header
Decoupling and bulk
Motor driver
MOTOR DRIVER SUBSYSTEM
NOTES
DRV8212P H-bridge, inputs straight from TIM1. VM = VSYS. Logic VCC is +3V3_DRV: the MCU's +3V3 through Rh2, a fitted 0R. Swap Rh2 for a ferrite (C108301, 600R at 100 MHz) if driver noise ever shows on the MCU rail, which is also the ADC reference. - Ch1-Ch5 return to GND, NOT PGND. This is on purpo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

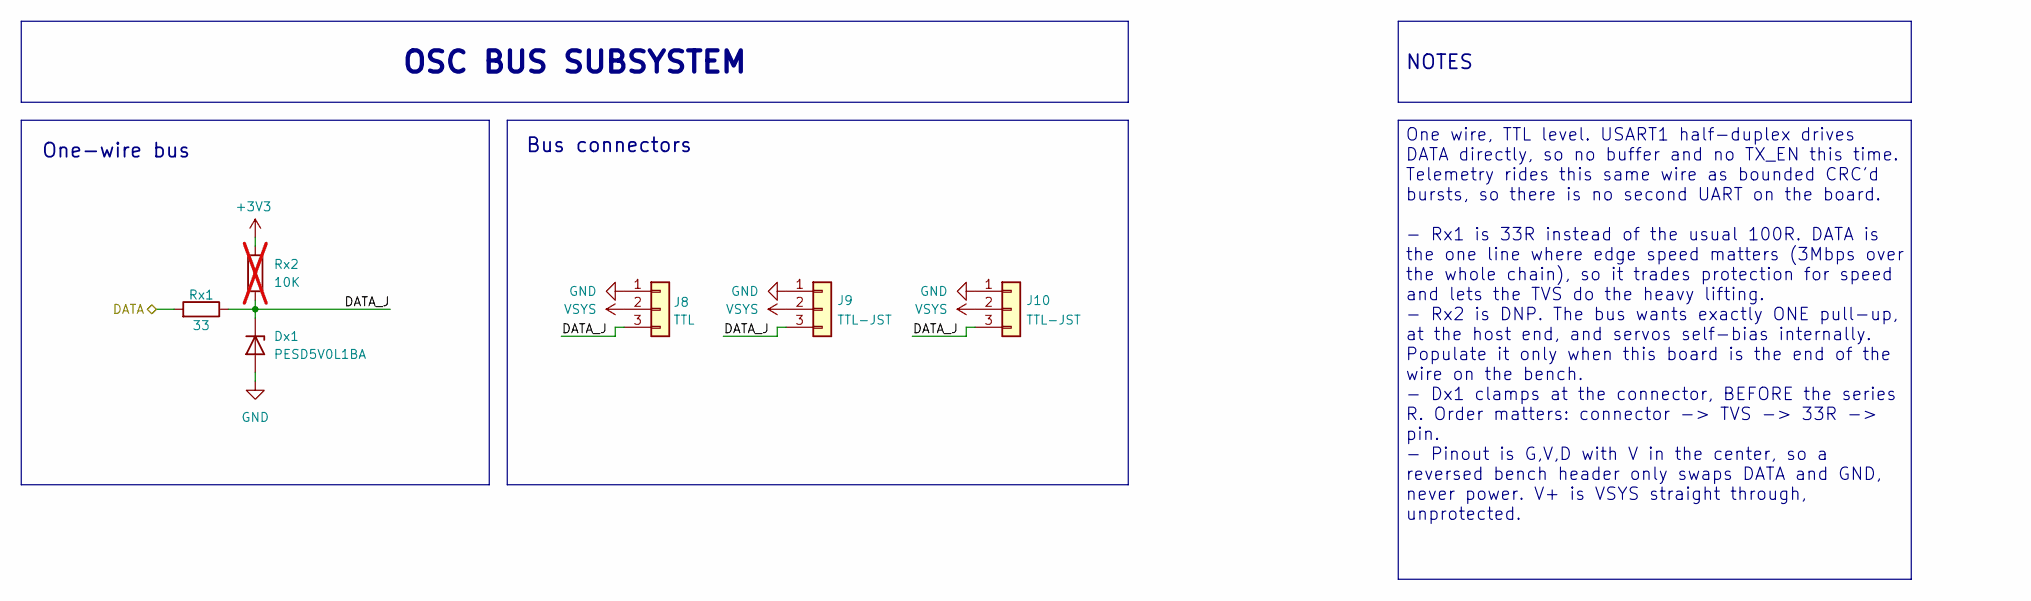
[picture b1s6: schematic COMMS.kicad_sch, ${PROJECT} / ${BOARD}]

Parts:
Dx1: PESD5V0L1BA; D_SOD-323_HandSoldering; LCSC C2687118
J8: TTL; PinHeader_1x03_P2.54mm_Vertical; LCSC C49257
J9, J10: TTL-JST; CONN-TH_B3B-PH-K-S; LCSC C131339
Rx1: 33; R_0603_1608Metric_Pad0.98x0.95mm_HandSolder; LCSC C108661
Rx2: 10K; R_0603_1608Metric_Pad0.98x0.95mm_HandSolder; LCSC C2906982; not fitted

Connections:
+3V3: Rx2.1; also elsewhere on the board
/COMMS/DATA: Rx1.2; also elsewhere on the board
/COMMS/DATA_J: Dx1.1 (K), J8.3, J9.3, J10.3, Rx1.1, Rx2.2
GND: Dx1.2 (A), J8.1, J9.1, J10.1; also elsewhere on the board
VSYS: J8.2, J9.2, J10.2; also elsewhere on the board

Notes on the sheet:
Bus connectors
One-wire bus
One wire, TTL level. USART1 half-duplex drives DATA directly, so no buffer and no TX_EN this time. Telemetry rides this same wire as bounded CRC'd bursts, so there is no second UART on the board. - Rx1 is 33R instead of the usual 100R. DATA is the one line where edge speed matters (3Mbps over the w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
OSC BUS SUBSYSTEM
NOTES
